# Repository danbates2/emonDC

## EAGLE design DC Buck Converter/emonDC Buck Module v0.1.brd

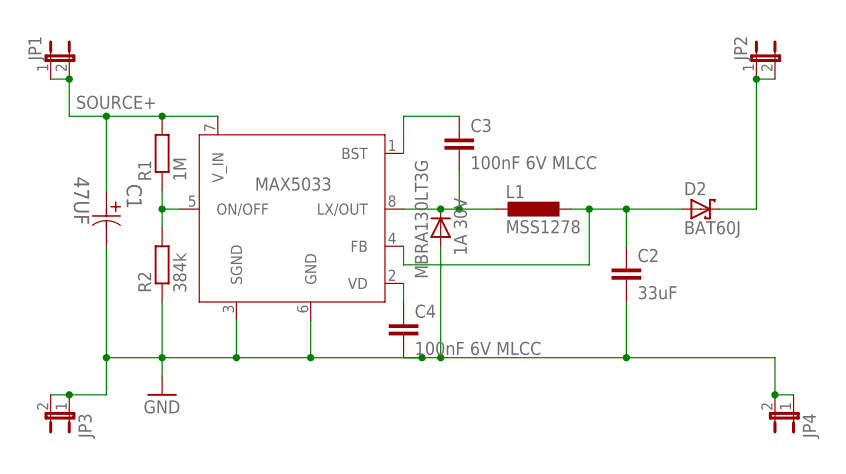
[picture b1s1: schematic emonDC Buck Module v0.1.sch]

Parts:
C1: 47UF; CAPAE1350X1400N
C2: 33uF; C1210; MPN TCQB336M006R0070
C3, C4: 100nF 6V MLCC; C0603
D1: MBRA130LT3G; DO-214; MPN MBRA130LT3G
D2: BAT60J; SOD323_ST
JP1, JP2, JP3, JP4: JP1E; JP1
L1: MSS1278; MPN MSS1278-224KLD
MAX5033: MAX5033BUSA+; 21-0111D_SBE-14
R1: 1M; R0603
R2: 384k; R0603

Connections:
+5V: D2.C, JP2.1, JP2.2
BST: C3.1, MAX5033.1 (BST)
FB: C2.1, D2.A, L1.P$1 (1), MAX5033.4 (FB)
GND: C1.2, C2.2, C4.2, D1.P$2 (A), JP3.1, JP3.2, JP4.1, JP4.2, MAX5033.3 (SGND), MAX5033.6 (GND), R2.1
ONOFF: MAX5033.5 (ON/OFF), R1.1, R2.2
OUT: C3.2, D1.P$1 (C), L1.P$2 (2), MAX5033.8 (LX/OUT)
SOURCE+: C1.1, JP1.1, JP1.2, MAX5033.7 (V_IN), R1.2
VD: C4.1, MAX5033.2 (VD)

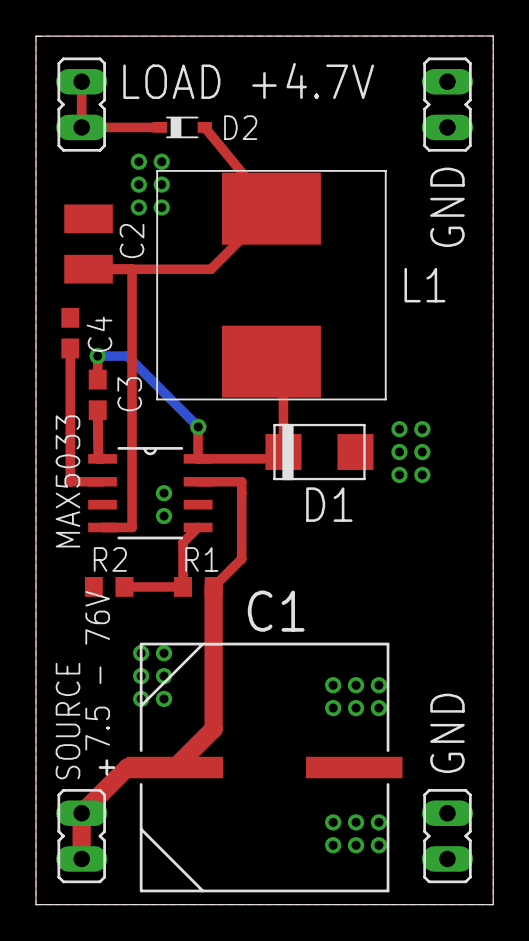
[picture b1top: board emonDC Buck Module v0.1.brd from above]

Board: 2 copper layers, 25.4 x 48.3 mm, 15 parts (1 on the bottom side), 8 nets.

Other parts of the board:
LOGO2: OSHW_LOGO_6MILX0200-NT; OSHW_6X200_NOTEXT

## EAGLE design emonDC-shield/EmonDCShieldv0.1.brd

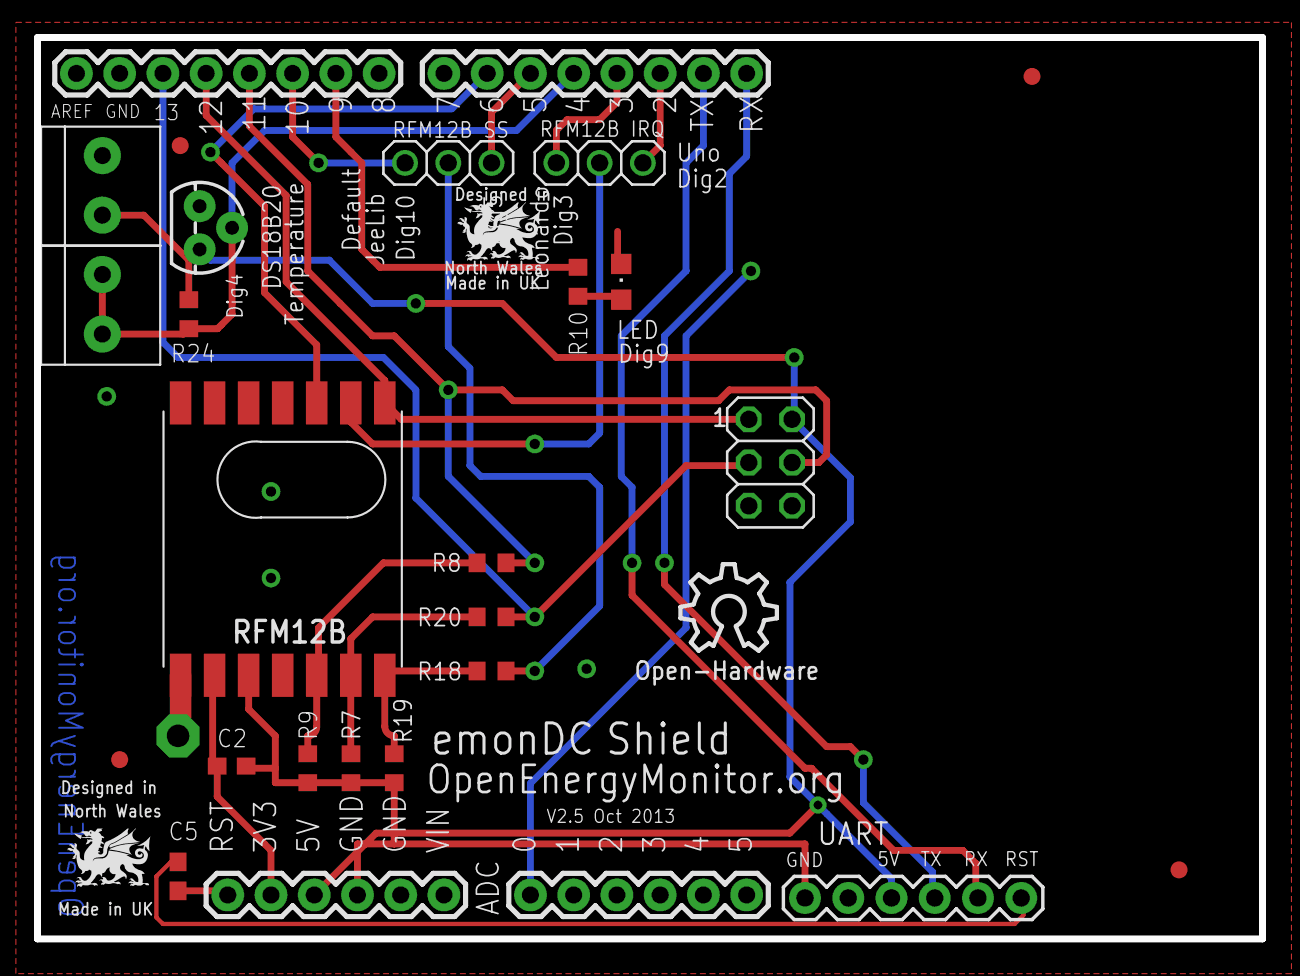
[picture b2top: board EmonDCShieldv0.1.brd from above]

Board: 2 copper layers, 72.0 x 53.0 mm, 26 parts (0 on the bottom side), 24 nets.

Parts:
ANT1: PAD-01
ARDUINO1: ARDUINO2
C2, C5: 100nF; C0603
ISP: 3x2F - BOTTOM; 2X03
J1, J2: 1X2-3.5MM
JP1, JP2: 1X03
JP3: FTDI_BASICPTH; FTDI_BASIC
LED: green; CHIPLED_0805
LOGO1: OSHW_LOGO_10MILX0200-NT; OSHW_10X200_NOTEXT
Q2: DS18B20; TO-92
R7, R9, R19: 10k; R0603
R8, R18, R20: 4k7; R0603
R10: 1K; R0603
R24: 4K7; R0603
U$1, U$3, U$4, U$5: FIDUCIAL; FIDUCIAL_1MM
U$2: RFM12B

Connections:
3.3V: ARDUINO1.3V3, C2.1, U$2.VDD
+5V: ARDUINO1.5V, ISP.2, J1.1, JP3.VCC, Q2.3, R24.1
DIG2: ARDUINO1.02, JP2.1
DIG3: ARDUINO1.PWM_03, JP2.3
DIG4: ARDUINO1.04, J2.1, J2.2, Q2.2, R24.2
DIG5: ARDUINO1.PWM_05, JP1.3
DIG6: ARDUINO1.PWM_06, U$2.FFS
DIG9: ARDUINO1.PWM_09, R10.2
DIG10: ARDUINO1.PWM_10, JP1.1
GND: ARDUINO1.GND, C2.2, ISP.6, J1.2, JP3.GND, LED.C, Q2.1, R7.1, R9.1, R19.1, U$2.GND
MISO: ARDUINO1.12, ISP.1, U$2.SDO
MOSI: ARDUINO1.PWM_11, ISP.4, R8.2
unnamed: JP2.2, U$2.IRQ
unnamed: JP1.2, R18.2
unnamed: C5.2, JP3.DTR
unnamed: LED.A, R10.1
unnamed: ANT1.1, U$2.ANT
unnamed: R7.2, R20.1, U$2.SCK
unnamed: R8.1, R9.2, U$2.SDI
unnamed: R18.1, R19.2, U$2.SEL
RST: ARDUINO1.RESET, C5.1
RX: ARDUINO1.RX_00, JP3.TXO
SCK: ARDUINO1.13, ISP.3, R20.2
TX: ARDUINO1.TX_01, JP3.RXI

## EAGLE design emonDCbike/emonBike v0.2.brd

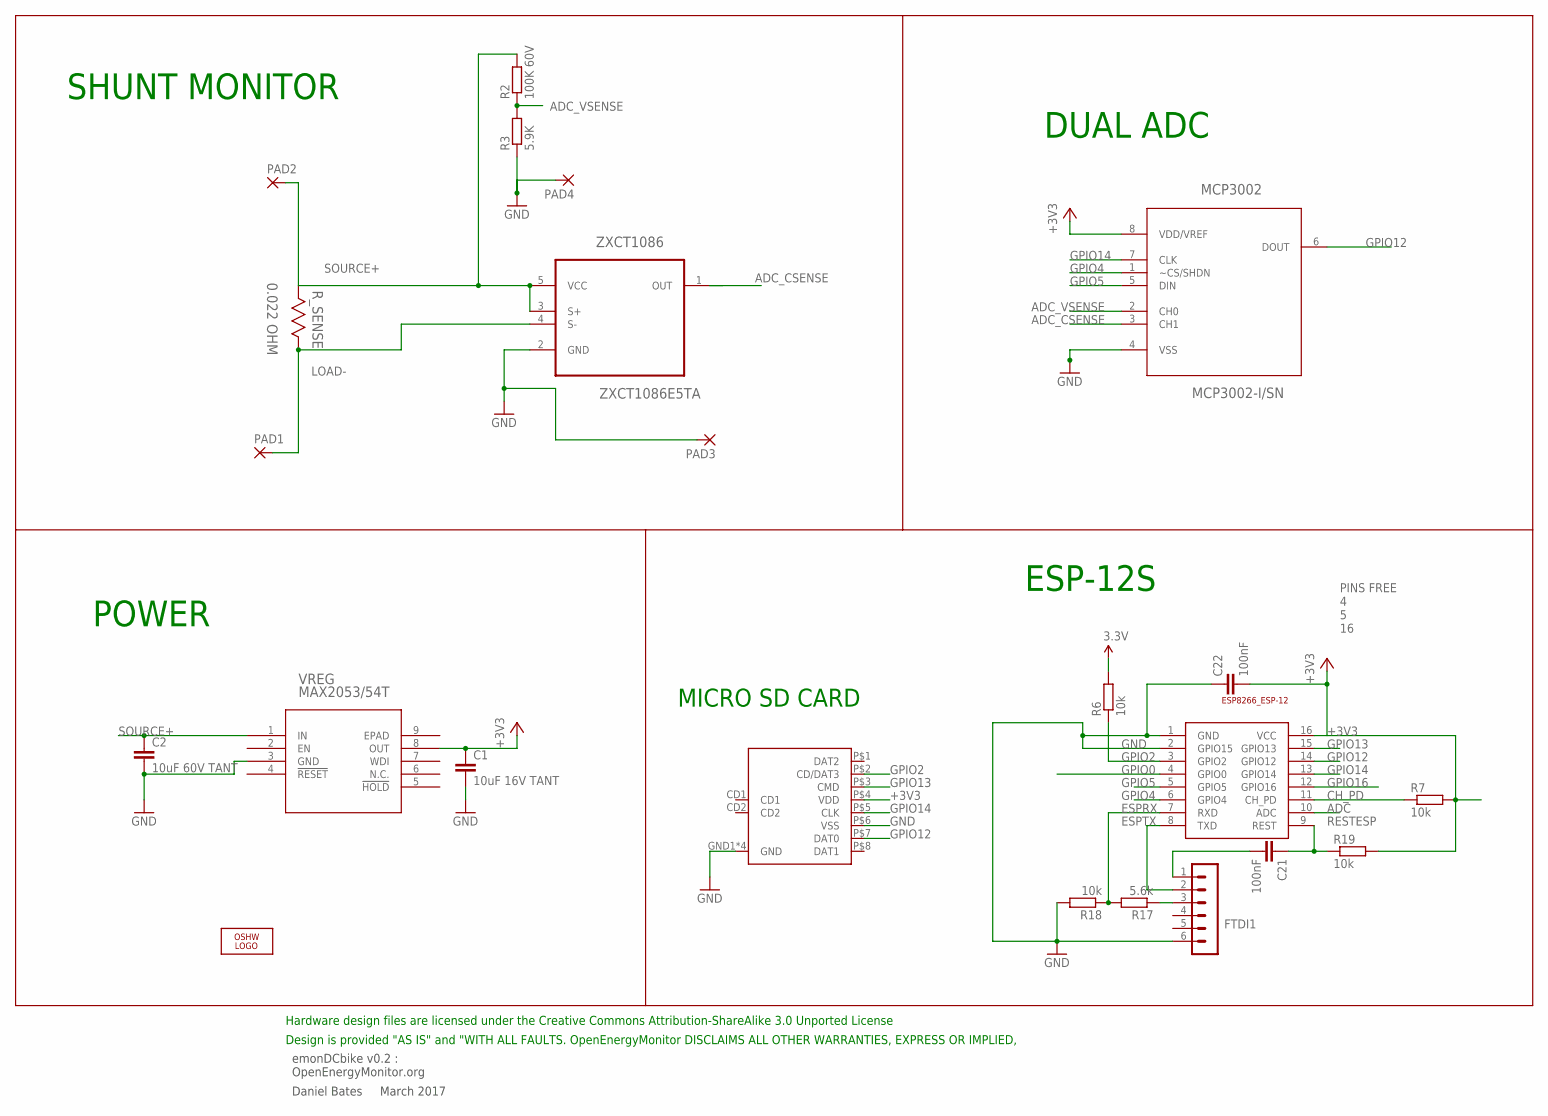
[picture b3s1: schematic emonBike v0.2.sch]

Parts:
C1: 10uF 16V TANT; C0603
C2: 10uF 60V TANT; C0603
C21, C22: 100nF; C0603
ESP-12: ESP8266_ESP-12; ESP8266-ESP12
FTDI1: FTDI-ESP; MA06-1
LOGO1: OSHW_LOGO_6MILX0200-NT; OSHW_6X200_NOTEXT
MAX2053: MAX5023TASA-T; 21-0111D_SBE-14
MCP3002: MCP3002-I/SN; SOIC127P600X175-8N
PAD1, PAD2, PAD3, PAD4: 3,81/1,4
R2: 100K 60V; R0603; MPN MCWR06X1003FTL
R3: 5.9K; R0603; MPN MCWR06X5901FTL
R6, R7, R18, R19: 10k; R0603
R17: 5.6k; R0603
R_SENSE: 0.022 OHM; RESC3216X71N
U$2: MOLEX_MICRO_SD_1040310811; MOLEX_MICROSD_EXPOSED
ZXCT1086: ZXCT1086E5TA; SOT95P280X130-5N

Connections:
+3V3: C1.1, C22.2, ESP-12.16 (VCC), MAX2053.8 (OUT), MCP3002.8 (VDD/VREF), R6.2, R7.2, R19.2, U$2.P$4 (VDD)
ADC: ESP-12.10 (ADC)
ADC_CSENSE: MCP3002.3 (CH1), ZXCT1086.1 (OUT)
ADC_VSENSE: MCP3002.2 (CH0), R2.1, R3.2
CH_PD: ESP-12.11 (CH_PD), R7.1
ESPRX: ESP-12.7 (RXD), R17.2, R18.1
ESPTX: ESP-12.8 (TXD), FTDI1.2
GND: C1.2, C2.2, C22.1, ESP-12.1 (GND), ESP-12.2 (GPIO15), FTDI1.6, MAX2053.3 (GND), MCP3002.4 (VSS), PAD3.1, PAD4.1, R3.1, R18.2, U$2.GND1 (GND), U$2.GND2 (GND), U$2.GND3 (GND), U$2.GND4 (GND), U$2.P$6 (VSS), ZXCT1086.2 (GND)
GPIO0: ESP-12.4 (GPIO0)
GPIO2: ESP-12.3 (GPIO2), R6.1, U$2.P$2 (CD/DAT3)
GPIO4: ESP-12.6 (GPIO4), MCP3002.1 (~CS/SHDN)
GPIO5: ESP-12.5 (GPIO5), MCP3002.5 (DIN)
GPIO12: ESP-12.14 (GPIO12), MCP3002.6 (DOUT), U$2.P$7 (DAT0)
GPIO13: ESP-12.15 (GPIO13), U$2.P$3 (CMD)
GPIO14: ESP-12.13 (GPIO14), MCP3002.7 (CLK), U$2.P$5 (CLK)
GPIO16: ESP-12.12 (GPIO16)
LOAD-: PAD1.1, R_SENSE.1 (R1), ZXCT1086.4 (S-)
unnamed: C21.2, FTDI1.1
unnamed: FTDI1.3, R17.1
RESTESP: C21.1, ESP-12.9 (REST), R19.1
SOURCE+: C2.1, MAX2053.1 (IN), PAD2.1, R2.2, R_SENSE.2 (R2), ZXCT1086.3 (S+), ZXCT1086.5 (VCC)

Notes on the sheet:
emonDCbike v0.2 : OpenEnergyMonitor.org
Daniel Bates March 2017
Design is provided "AS IS" and "WITH ALL FAULTS. OpenEnergyMonitor DISCLAIMS ALL OTHER WARRANTIES, EXPRESS OR IMPLIED,
Hardware design files are licensed under the Creative Commons Attribution-ShareAlike 3.0 Unported License
SHUNT MONITOR
ESP-12S
MICRO SD CARD
PINS FREE 4 5 16
POWER
DUAL ADC

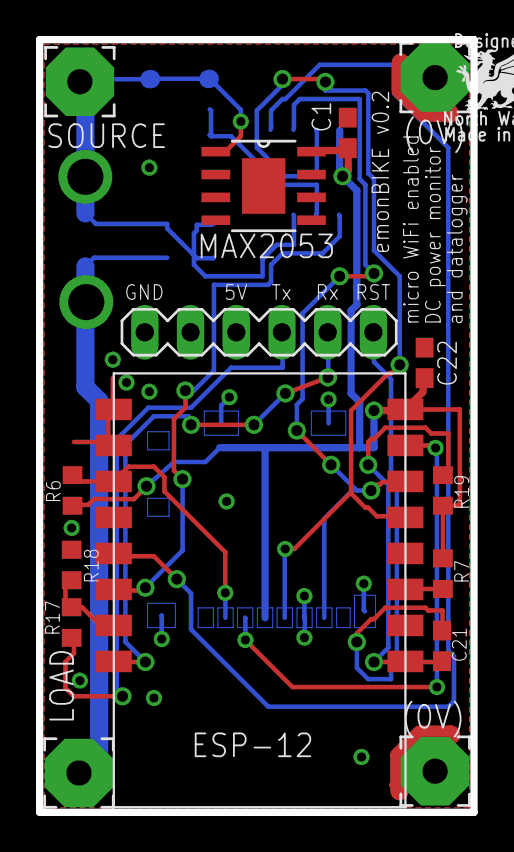
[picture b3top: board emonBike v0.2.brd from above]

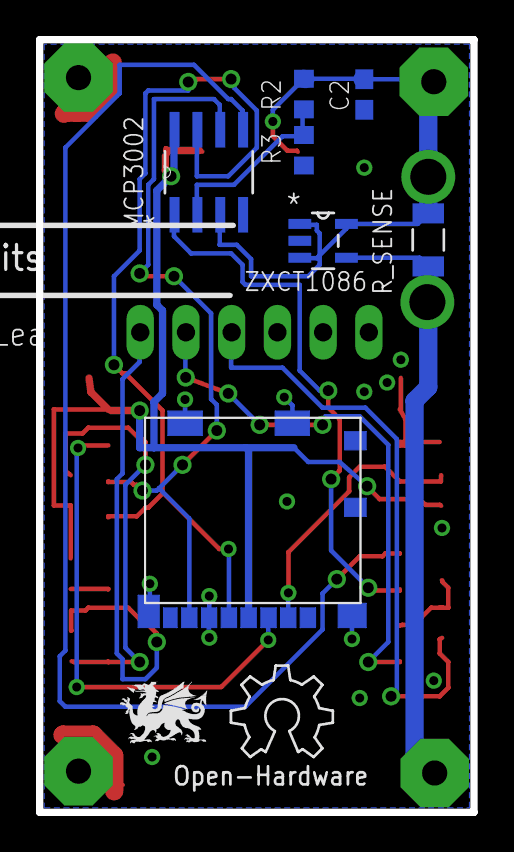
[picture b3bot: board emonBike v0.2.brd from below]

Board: 2 copper layers, 24.1 x 42.9 mm, 24 parts (9 on the bottom side), 18 nets.

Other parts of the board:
U$3: DRAGON_LOGO_NOTEXT

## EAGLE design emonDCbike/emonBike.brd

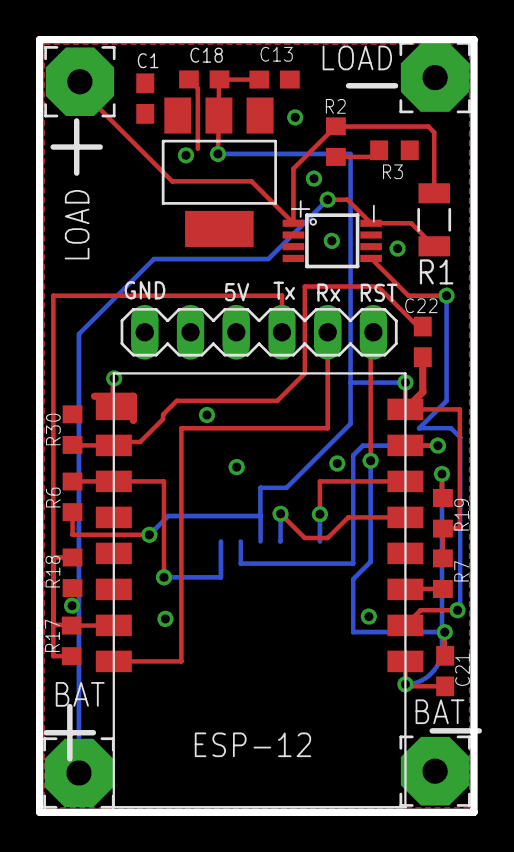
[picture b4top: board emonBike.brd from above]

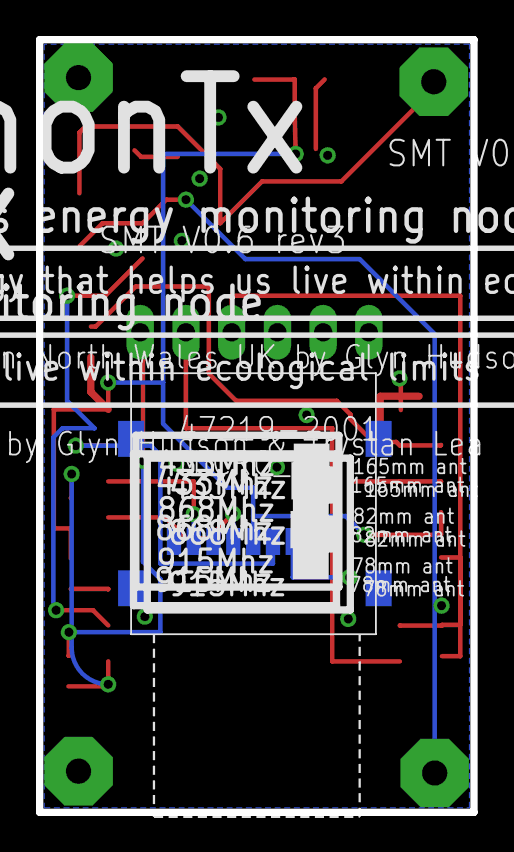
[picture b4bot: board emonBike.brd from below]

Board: 2 copper layers, 24.1 x 42.9 mm, 24 parts (2 on the bottom side), 18 nets.

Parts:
3.3V_REG: REG1117; SOT223
C1, C18: 10uF TANT; C0603
C13, C21, C22: 100nF; C0603
ESP-12: ESP8266_ESP-12; ESP8266-ESP12
FTDI1: FTDI-ESP; MA06-1
LOGO1: OSHW_LOGO_6MILX0200-NT; OSHW_6X200_NOTEXT
PAD1, PAD2, PAD3, PAD4: 3,81/1,4
R1: 0.022 OHM; RESC3216X71N
R2: 100K 60V; R0603
R3: 5.9K; R0603
R6, R7, R18, R19, R30: 10k; R0603
R17: 5.6k; R0603
SHUNTMON-A: LMP8481; S-PDSO-G08
U$1: 47219-2001_MICROSD

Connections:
3.3V: 3.3V_REG.2, C13.1, C18.1, C22.2, ESP-12.16, R6.2, R7.2, R19.2, U$1.PIN4
5.0V: 3.3V_REG.3, C1.1
ADC: ESP-12.10, SHUNTMON-A.5
ADCVSENSE-A: R2.1, R3.2
CH_PD: ESP-12.11, R7.1
ESPRX: ESP-12.7, R17.2, R18.1
ESPTX: ESP-12.8, FTDI1.2
GND: 3.3V_REG.1, C1.2, C13.2, C18.2, FTDI1.6, PAD3.1, PAD4.1, R3.1, R18.2, R30.1, SHUNTMON-A.4, SHUNTMON-A.6, SHUNTMON-A.7, U$1.P$1, U$1.P$2, U$1.P$3, U$1.P$4, U$1.PIN6
GPIO2: ESP-12.3, R6.1, U$1.PIN2
GPIO12: ESP-12.14, U$1.PIN7
GPIO13: ESP-12.15, U$1.PIN3
GPIO14: ESP-12.13, U$1.PIN5
GPIO15: C22.1, ESP-12.1, ESP-12.2, R30.2
INPUT-POS-A: PAD2.1, R1.2, R2.2, SHUNTMON-A.1
LOAD-NEG-A: PAD1.1, R1.1, SHUNTMON-A.8
unnamed: C21.2, FTDI1.1
unnamed: FTDI1.3, R17.1
RESTESP: C21.1, ESP-12.9, R19.1

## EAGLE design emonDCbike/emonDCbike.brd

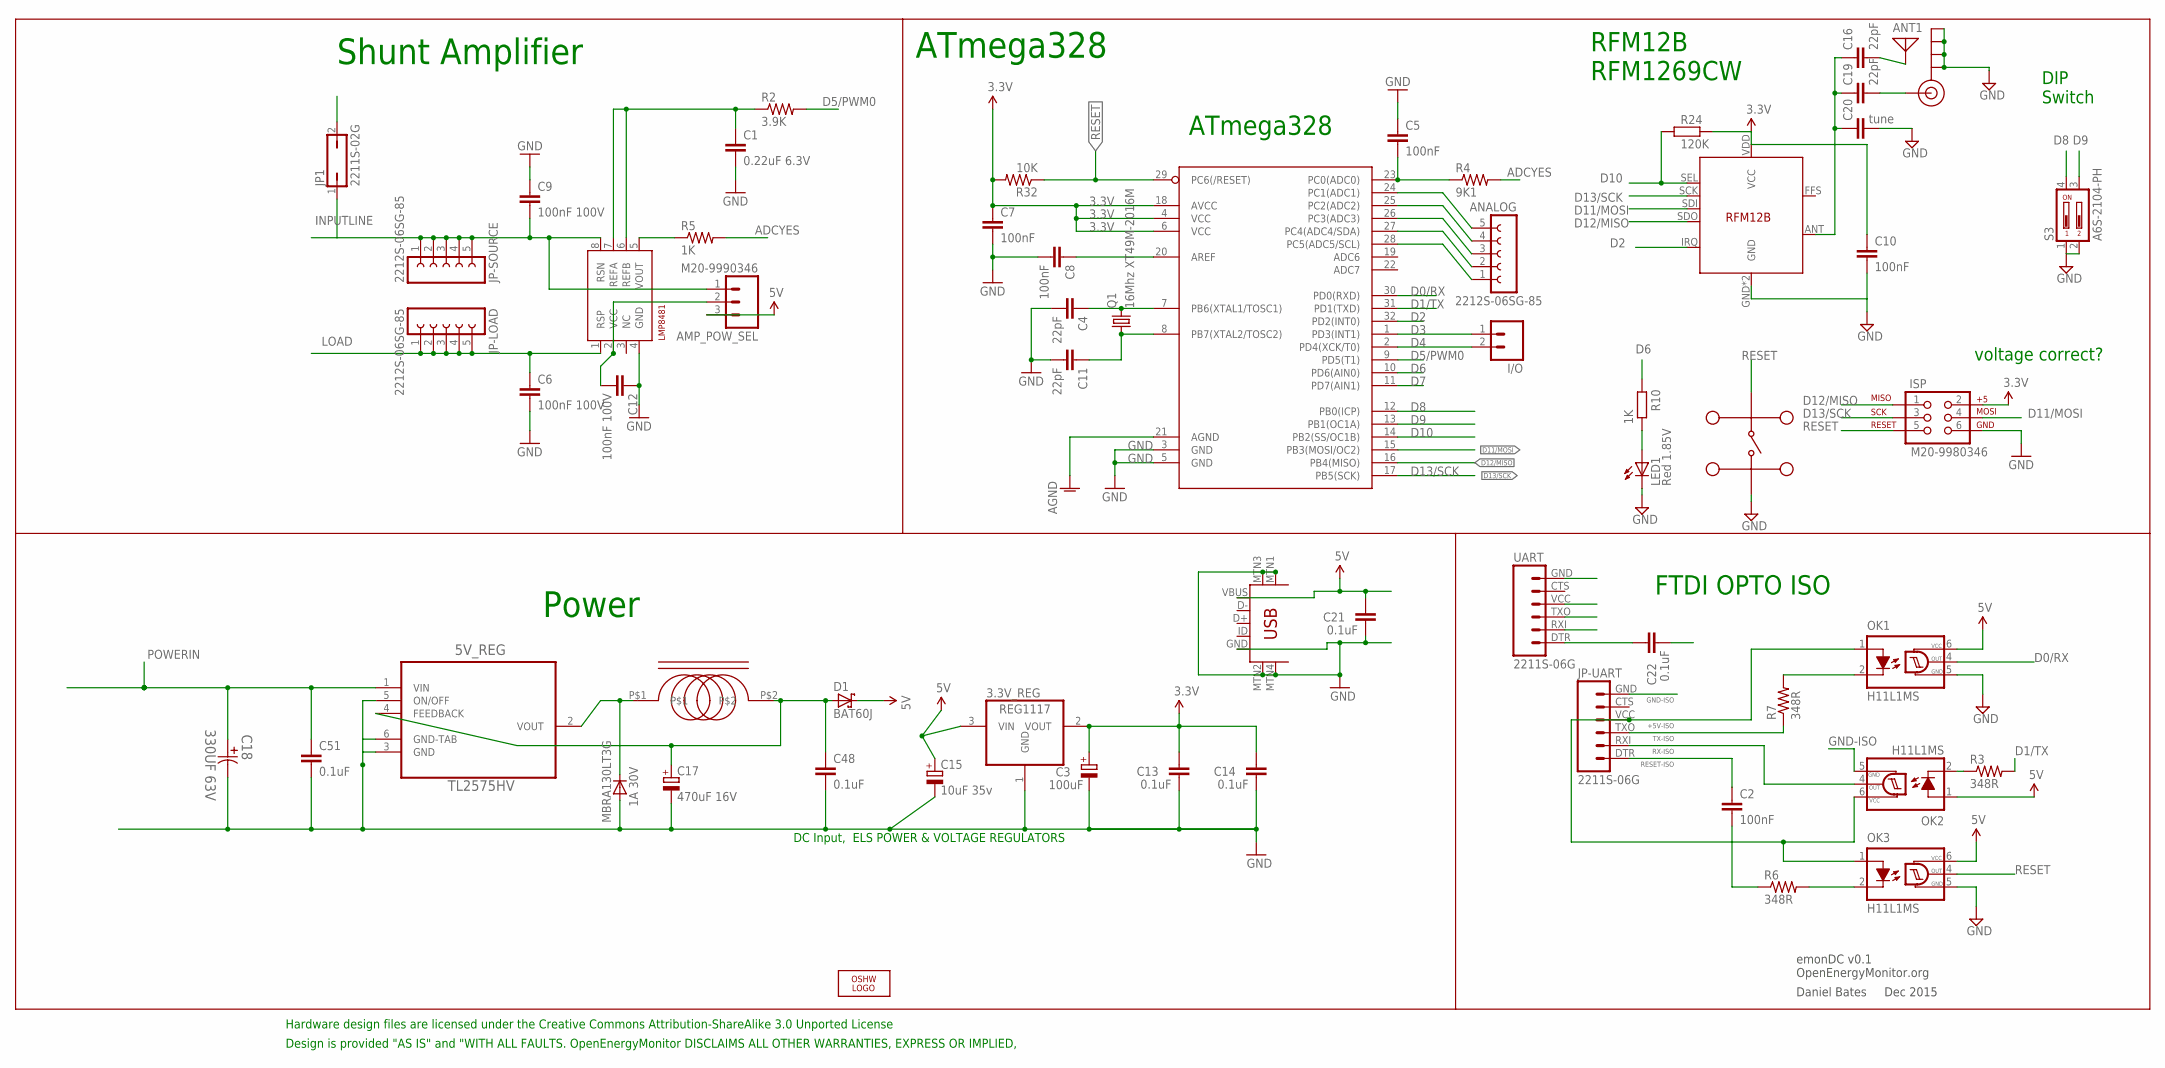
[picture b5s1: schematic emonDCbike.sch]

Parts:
3.3V_REG: REG1117; SOT223
5V_REG: TL2575HV; TO-263; MPN LM2575HVS-15/NOPB
AMP_POW_SEL: M20-9990346; 1X03_SMD_RA_FEMALE_NOWRITE; MPN M20-9990346
ANALOG: 2212S-06SG-85; FE05-1; MPN 2212S-06SG-85
ANT1: ANTENNA; PAD-01
C1: 0.22uF 6.3V; C0402K; MPN 04026D224KAT2A
C2, C5, C7, C8, C10: 100nF; C0402K; MPN 0402X104K100CT
C3: 100uF; 153CLV-0605; MPN UWX0J101MCL1GB
C4, C11, C16, C19: 22pF; C0603; MPN CC0402JRNPO9BN470
C6, C9, C12: 100nF 100V; C0805K; MPN 08051C104K4Z2A
C13, C14, C21, C22, C48: 0.1uF; C0805K; MPN 0805B104K160CT
C15: 10uF 35v; E1,8-4; MPN TAJD106K035RNJ
C17: 470uF 16V; E3,5-8; MPN 16YXF470MEFC10X12.5
C18: 330UF 63V; CAPPR500-1000X2000
C20: tune; C0603
C51: 0.1uF; C0805; MPN 0805B104K160CT
D1: BAT60J; SOD323_ST
D2: MBRA130LT3G; DO-214; MPN MBRA130LT3G
I1: SRR0603-331KL; MPN SRR0603-331KL
I/O: 2212S-02SG-85; 1X02_LOCK; MPN 2212S-02SG-85
ISP: M20-9980346; 2X3; MPN M20-9980346
J$1: SMA_EDGE; SMA-EDGE
JP1: 2211S-02G; JP1; MPN 2211S-02G
JP-LOAD: 2212S-06SG-85; FE05-1; MPN 2212S-06SG-85
JP-SOURCE: 2212S-06SG-85; FE05-1; MPN 2212S-06SG-85
JP-UART: 2211S-06G; FTDI_BASIC; MPN 2211S-06G
LED1: Red 1.85V; CHIP-LED0805; MPN SML-211UTT86K
LMP8481: LMP8481SMCLMP8481; S-PDSO-G08; MPN LMP8481MME-S/NOPB
LOGO1: OSHW_LOGO_6MILX0200-NT; OSHW_6X200_NOTEXT
OK1, OK2, OK3: H11L1MS; DIL6-SMD
Q1: 16Mhz XT49M-2016M; HC49UP; MPN XT49M-2016M
R2: 3.9K; R0603; MPN CRCW06039K09FKEA
R3, R6, R7: 348R; R0603; MPN MC0063W06031348R
R4: 9K1; R0603; MPN MC01W080559K1
R5, R10: 1K; R0603; MPN MC0063W060351K
R24: 120K; R0603; MPN RC0603FR-07120KL
R32: 10K; R0603; MPN MC0063W0603510K
RF: RFM12B
S3: A6S-2104-PH; DIP_SWITCH_SMT; MPN A6S2104H
U1_TQFP: ATMEGA328P; TQFP32-08; MPN ATMEGA328-AU
U$1: MC32882; SWITCH_TACT_MULTICOMP
UART: 2211S-06G; FTDI_BASIC; MPN 2211S-06G
USB: MUSB-05-S-B-SM-A; USB-MINIB-CISECO; MPN 67503-1020

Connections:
3.3V: 3.3V_REG.2 (VOUT), C3.+, C7.1, C10.1, C13.1, C14.1, ISP.2, R24.2, R32.2, RF.VDD (VCC), U1_TQFP.4 (VCC), U1_TQFP.6 (VCC), U1_TQFP.18 (AVCC)
5VHIGH: 5V_REG.4 (FEEDBACK), C17.+, C48.1, D1.A, I1.P$2
5VLOW: 3.3V_REG.3 (VIN), AMP_POW_SEL.3, C15.+, C21.1, D1.C, OK1.6 (VCC), OK2.1 (A), OK3.6 (VCC), UART.VCC (4), USB.VBUS
+5V-ISO: JP-UART.VCC (4), OK1.1 (A), OK2.6 (VCC), OK3.1 (A)
ADC1: ANALOG.5, U1_TQFP.24 (PC1(ADC1))
ADC2: ANALOG.4, U1_TQFP.25 (PC2(ADC2))
ADC3: ANALOG.3, U1_TQFP.26 (PC3(ADC3))
ADC4: ANALOG.2, U1_TQFP.27 (PC4(ADC4/SDA))
ADC5: ANALOG.1, U1_TQFP.28 (PC5(ADC5/SCL))
ADCYES: R4.2, R5.2
AGND: U1_TQFP.21 (AGND)
D0/RX: OK1.4 (OUT), U1_TQFP.30 (PD0(RXD)), UART.TXO (3)
D1/TX: R3.2, U1_TQFP.31 (PD1(TXD)), UART.RXI (2)
D2: RF.IRQ, U1_TQFP.32 (PD2(INT0))
D3: I/O.1, U1_TQFP.1 (PD3(INT1))
D4: I/O.2, U1_TQFP.2 (PD4(XCK/T0))
D5/PWM0: R2.2, U1_TQFP.9 (PD5(T1))
D6: R10.2, U1_TQFP.10 (PD6(AIN0))
D7: U1_TQFP.11 (PD7(AIN1))
D8: S3.4, U1_TQFP.12 (PB0(ICP))
D9: S3.3, U1_TQFP.13 (PB1(OC1A))
D9/PWM1: C1.1, LMP8481.6 (REFB), LMP8481.7 (REFA), R2.1
D10: R24.1, RF.SEL, U1_TQFP.14 (PB2(SS/OC1B))
D11/MOSI: ISP.4, RF.SDI, U1_TQFP.15 (PB3(MOSI/OC2))
D12/MISO: ISP.1, RF.SDO, U1_TQFP.16 (PB4(MISO))
D13/SCK: ISP.3, RF.SCK, U1_TQFP.17 (PB5(SCK))
DIG1: C16.1, C19.1, C20.1, RF.ANT
GND: 3.3V_REG.1 (GND), 5V_REG.3 (GND), 5V_REG.5 (ON/OFF), 5V_REG.6 (GND-TAB), C1.2, C3.-, C4.2, C5.1, C6.2, C7.2, C8.2, C9.1, C10.2, C11.2, C12.1, C13.2, C14.2, C15.-, C17.-, C18.2, C20.2, C21.2, C48.2, C51.2, D2.P$2 (A), ISP.6, J$1.GND@0 (GND), J$1.GND@1 (GND), J$1.GND@2 (GND), J$1.GND@3 (GND), LED1.C, LMP8481.4 (GND), OK1.5 (GND), OK3.5 (GND), RF.GND, RF.P$12 (GND), S3.1, S3.2, U1_TQFP.3 (GND), U1_TQFP.5 (GND), U$1.P$3, U$1.P$4, UART.GND (6), USB.GND, USB.MTN1 (MTN2), USB.MTN2 (MTN3), USB.MTN3 (MTN1), USB.MTN4
GND-ISO: JP-UART.GND (6), OK2.5 (GND)
IND: 5V_REG.2 (VOUT), D2.P$1 (C), I1.P$1
INPUTLINE: AMP_POW_SEL.1, C9.2, JP1.1, JP-SOURCE.1, JP-SOURCE.2, JP-SOURCE.3, JP-SOURCE.4, JP-SOURCE.5, LMP8481.8 (RSN)
LOAD: C6.1, JP-LOAD.1, JP-LOAD.2, JP-LOAD.3, JP-LOAD.4, JP-LOAD.5, LMP8481.1 (RSP)
unnamed: C4.1, Q1.2, U1_TQFP.7 (PB6(XTAL1/TOSC1))
unnamed: C5.2, R4.1, U1_TQFP.23 (PC0(ADC0))
unnamed: C22.1, UART.DTR (1)
unnamed: LMP8481.5 (VOUT), R5.1
unnamed: AMP_POW_SEL.2, C12.2, LMP8481.2 (VCC)
unnamed: C11.1, Q1.1, U1_TQFP.8 (PB7(XTAL2/TOSC2))
unnamed: C2.1, JP-UART.DTR (1)
unnamed: ANT1.1, C16.2
unnamed: OK1.2 (C), R7.2
unnamed: OK2.2 (C), R3.1
unnamed: OK3.2 (C), R6.2
unnamed: C8.1, U1_TQFP.20 (AREF)
unnamed: C19.2, J$1.SIG (SIGNAL)
unnamed: LED1.A, R10.1
POWERIN: 5V_REG.1 (VIN), C18.1, C51.1, JP1.2
RESET: C22.2, ISP.5, OK3.4 (OUT), R32.1, U1_TQFP.29 (PC6(/RESET)), U$1.P$1, U$1.P$2
RESET-ISO: C2.2, R6.1
RX-ISO: JP-UART.RXI (2), OK2.4 (OUT)
TX-ISO: JP-UART.TXO (3), R7.1

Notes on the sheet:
emonDC v0.1 OpenEnergyMonitor.org
Daniel Bates Dec 2015
Power
ATmega328
Design is provided "AS IS" and "WITH ALL FAULTS. OpenEnergyMonitor DISCLAIMS ALL OTHER WARRANTIES, EXPRESS OR IMPLIED,
Hardware design files are licensed under the Creative Commons Attribution-ShareAlike 3.0 Unported License
RFM12B RFM1269CW
DIP Switch
FTDI OPTO ISO
DC Input, ELS POWER & VOLTAGE REGULATORS
Shunt Amplifier
voltage correct?

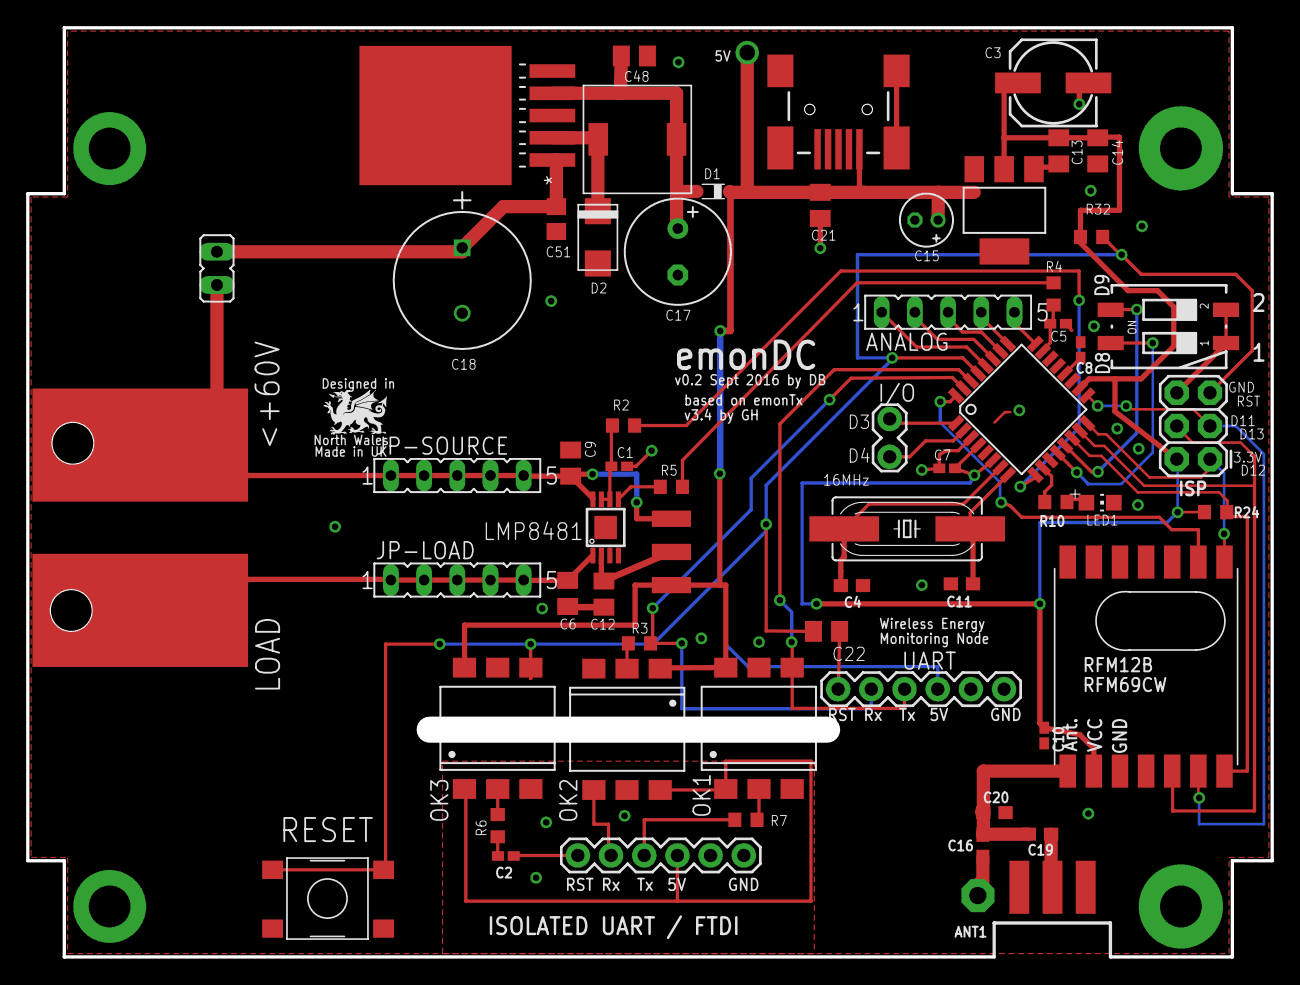
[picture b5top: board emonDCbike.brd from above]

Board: 2 copper layers, 95.2 x 71.1 mm, 61 parts (1 on the bottom side), 49 nets.

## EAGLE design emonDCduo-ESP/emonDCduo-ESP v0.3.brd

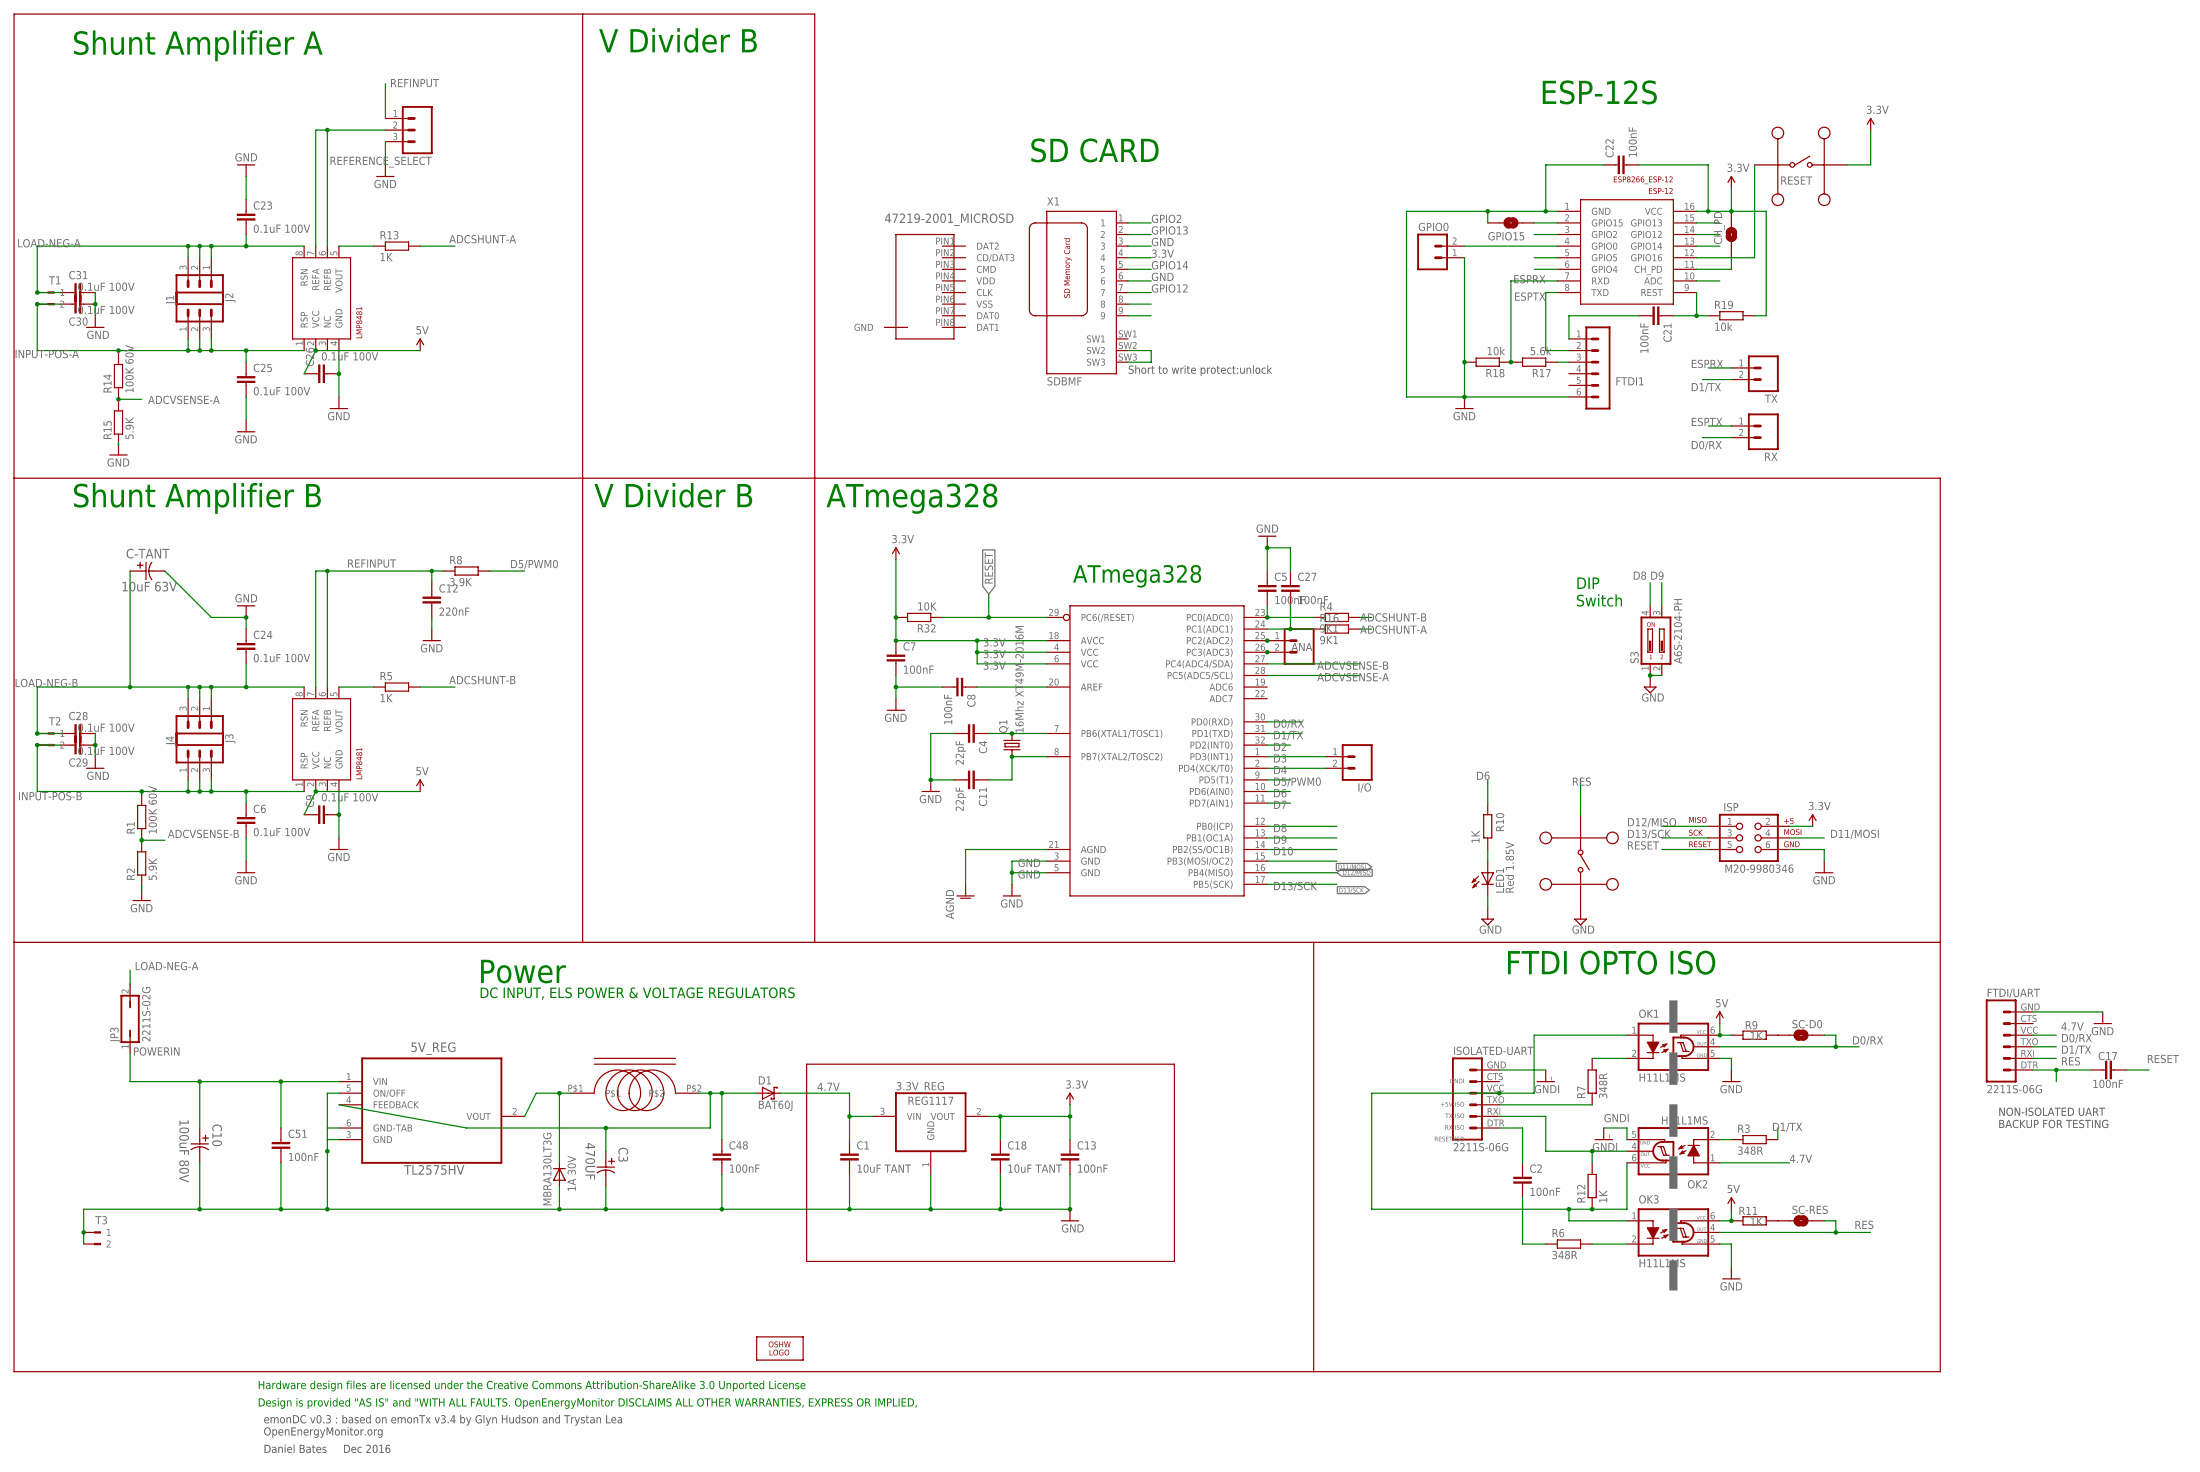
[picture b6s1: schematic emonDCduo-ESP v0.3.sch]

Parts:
3.3V_REG: REG1117; SOT223
5V_REG: TL2575HV; TO-263; MPN LM2575HVS-15/NOPB
ANA: 2212S-02SG-85; 1X02_LOCK; MPN 2212S-02SG-85
C1, C18: 10uF TANT; C0603
C2, C5, C7, C8, C13, C17, C21, C22, C27, C48, C51: 100nF; C0603
C3: 470UF; CAPAE830X1050N
C4, C11: 22pF; C0603
C6, C9, C23, C24, C25, C26, C28, C29, C30, C31: 0.1uF 100V; C0603; MPN C1608X7S2A104K080AB
C10: 100uF 80V; CAPAE1350X1400N
C12: 220nF; C0603
C-TANT: 10uF 63V; 2917; PARTNO 293D106X0063E2TE3
CH_PD: SOLDERJUMPERNO; SJ_2S-NO
D1: BAT60J; SOD323_ST
D2: MBRA130LT3G; DO-214; MPN MBRA130LT3G
ESP-12: ESP8266_ESP-12; ESP8266-ESP12
FTDI1: FTDI-ESP; MA06-1
FTDI/UART: 2211S-06G; FTDI_BASIC; MPN 2211S-06G
GPIO0: M02PTH; 1X02
GPIO15: SOLDERJUMPERNO; SJ_2S-NO
I1: SRR0603-331KL; MPN SRR0603-331KL
I/O: 2212S-02SG-85; 1X02_LOCK; MPN 2212S-02SG-85
ISOLATED-UART: 2211S-06G; FTDI_BASIC; MPN 2211S-06G
ISP: M20-9980346; 2X3; MPN M20-9980346
J1, J2, J3, J4: CONN_03; 1X03
JP3: 2211S-02G; JP1; MPN 2211S-02G
LED1: Red 1.85V; CHIP-LED0805; MPN SML-211UTT86K
LOGO1: OSHW_LOGO_6MILX0200-NT; OSHW_6X200_NOTEXT
MC1, MC32882: MC32882; SWITCH_TACT_MULTICOMP
OK1, OK2, OK3: H11L1MS; DIL6-SMD
Q1: 16Mhz XT49M-2016M; HC49UP; MPN XT49M-2016M
R1, R14: 100K 60V; R0603; MPN MCWR06X1003FTL
R2, R15: 5.9K; R0603; MPN MCWR06X5901FTL
R3, R6, R7: 348R; R0603
R4, R16: 9K1; R0603
R5, R9, R10, R11, R12, R13: 1K; R0603
R8: 3.9K; R0603
R17: 5.6k; R0603
R18, R19: 10k; R0603
R32: 10K; R0603
REFERENCE_SELECT: 2212S-02SG-85; 1X03; MPN 2212S-02SG-85
RX: M02PTH; 1X02
S3: A6S-2104-PH; DIP_SWITCH_SMT; MPN A6S2104H
SC-D0: SOLDERJUMPERNO; SJ_2S-NO
SC-RES: SOLDERJUMPERNO; SJ_2S-NO
SHUNTMON-A: LMP8481; S-PDSO-G08; MPN LMP8481MME-S/NOPB
SHUNTMON-B: LMP8481; S-PDSO-G08; MPN LMP8481MME-H/NOPB
T1, T2, T3: 180-2
TX: M02PTH; 1X02
U1_TQFP: ATMEGA328P; TQFP32-08; MPN ATMEGA328P-AU
U$1: 47219-2001_MICROSD
X1: SDBMF; SDBMF-009XXBXX2

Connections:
3.3V: 3.3V_REG.2 (VOUT), C7.1, C13.1, C18.1, C22.2, CH_PD.1, ESP-12.16 (VCC), ISP.2, MC1.P$3, MC1.P$4, R19.2, R32.2, U1_TQFP.4 (VCC), U1_TQFP.6 (VCC), U1_TQFP.18 (AVCC), X1.4
4.7V: 3.3V_REG.3 (VIN), C1.1, C9.1, C26.1, D1.C, FTDI/UART.VCC (4), OK1.6 (VCC), OK2.1 (A), OK3.6 (VCC), R9.2, R11.2, SHUNTMON-A.2 (VCC), SHUNTMON-B.2 (VCC)
5.0V: 5V_REG.4 (FEEDBACK), C3.1, C48.1, D1.A, I1.P$2
+5V-ISO: ISOLATED-UART.VCC (4), OK1.1 (A), OK2.6 (VCC), OK3.1 (A), R12.1
ADC2: ANA.1, U1_TQFP.25 (PC2(ADC2))
ADC3: ANA.2, U1_TQFP.26 (PC3(ADC3))
ADCSHUNT-A: R13.2, R16.2
ADCSHUNT-B: R4.2, R5.2
ADCVSENSE-A: R14.1, R15.2, U1_TQFP.28 (PC5(ADC5/SCL))
ADCVSENSE-B: R1.1, R2.2, U1_TQFP.27 (PC4(ADC4/SDA))
AGND: U1_TQFP.21 (AGND)
D0/RX: FTDI/UART.TXO (3), OK1.4 (OUT), RX.2, SC-D0.1, U1_TQFP.30 (PD0(RXD))
D1/TX: FTDI/UART.RXI (2), R3.2, TX.2, U1_TQFP.31 (PD1(TXD))
D2: U1_TQFP.32 (PD2(INT0))
D3: I/O.1, U1_TQFP.1 (PD3(INT1))
D4: I/O.2, U1_TQFP.2 (PD4(XCK/T0))
D5/PWM0: R8.2, U1_TQFP.9 (PD5(T1))
D6: R10.2, U1_TQFP.10 (PD6(AIN0))
D7: U1_TQFP.11 (PD7(AIN1))
D8: S3.4, U1_TQFP.12 (PB0(ICP))
D9: S3.3, U1_TQFP.13 (PB1(OC1A))
D10: U1_TQFP.14 (PB2(SS/OC1B))
D11/MOSI: ISP.4, U1_TQFP.15 (PB3(MOSI/OC2))
D12/MISO: ISP.1, U1_TQFP.16 (PB4(MISO))
D13/SCK: ISP.3, U1_TQFP.17 (PB5(SCK))
ESPRX: ESP-12.7 (RXD), R17.2, R18.1, TX.1
ESPTX: ESP-12.8 (TXD), FTDI1.2, RX.1
GND: 3.3V_REG.1 (GND), 5V_REG.3 (GND), 5V_REG.5 (ON/OFF), 5V_REG.6 (GND-TAB), C1.2, C3.2, C4.2, C5.1, C6.2, C7.2, C8.2, C9.2, C10.2, C11.2, C12.2, C13.2, C18.2, C22.1, C23.1, C24.1, C25.2, C26.2, C27.1, C28.2, C29.2, C30.2, C31.2, C48.2, C51.2, C-TANT.2, D2.P$2 (A), ESP-12.1 (GND), FTDI1.6, FTDI/UART.GND (6), GPIO0.1, GPIO15.2, ISP.6, LED1.C, MC32882.P$3, MC32882.P$4, OK1.5 (GND), OK3.5 (GND), R2.1, R15.1, R18.2, REFERENCE_SELECT.3, S3.1, S3.2, SHUNTMON-A.4 (GND), SHUNTMON-B.4 (GND), T3.1, T3.2, U1_TQFP.3 (GND), U1_TQFP.5 (GND), X1.3, X1.6
GNDI: ISOLATED-UART.GND (6), OK2.5 (GND)
GPIO2: ESP-12.3 (GPIO2), X1.1
GPIO4: ESP-12.6 (GPIO4)
GPIO5: ESP-12.5 (GPIO5)
GPIO12: ESP-12.14 (GPIO12), X1.7
GPIO13: ESP-12.15 (GPIO13), X1.2
GPIO14: ESP-12.13 (GPIO14), X1.5
GPIO16: ESP-12.12 (GPIO16), MC1.P$1, MC1.P$2
IND: 5V_REG.2 (VOUT), D2.P$1 (C), I1.P$1
INPUT-POS-A: C25.1, C30.1, J2.1, J2.2, J2.3, R14.2, SHUNTMON-A.1 (RSP), T1.2
INPUT-POS-B: C6.1, C29.1, J3.1, J3.2, J3.3, R1.2, SHUNTMON-B.1 (RSP), T2.2
LOAD-NEG-A: C23.2, C31.1, J1.1, J1.2, J1.3, JP3.2, SHUNTMON-A.8 (RSN), T1.1
LOAD-NEG-B: C24.2, C28.1, C-TANT.1, J4.1, J4.2, J4.3, SHUNTMON-B.8 (RSN), T2.1
unnamed: C4.1, Q1.2, U1_TQFP.7 (PB6(XTAL1/TOSC1))
unnamed: C5.2, R4.1, U1_TQFP.23 (PC0(ADC0))
unnamed: R11.1, SC-RES.2
unnamed: R13.1, SHUNTMON-A.5 (VOUT)
unnamed: R9.1, SC-D0.2
unnamed: R5.1, SHUNTMON-B.5 (VOUT)
unnamed: ESP-12.2 (GPIO15), GPIO15.1
unnamed: C11.1, Q1.1, U1_TQFP.8 (PB7(XTAL2/TOSC2))
unnamed: C2.1, ISOLATED-UART.DTR (1)
unnamed: X1.SW2, X1.SW3
unnamed: OK1.2 (C), R7.2
unnamed: OK2.2 (C), R3.1
unnamed: OK3.2 (C), R6.2
unnamed: C8.1, U1_TQFP.20 (AREF)
unnamed: C27.2, R16.1, U1_TQFP.24 (PC1(ADC1))
unnamed: REFERENCE_SELECT.2, SHUNTMON-A.6 (REFB), SHUNTMON-A.7 (REFA)
unnamed: ESP-12.4 (GPIO0), GPIO0.2
unnamed: C21.2, FTDI1.1
unnamed: FTDI1.3, R17.1
unnamed: CH_PD.2, ESP-12.11 (CH_PD)
unnamed: C21.1, ESP-12.9 (REST), R19.1
unnamed: LED1.A, R10.1
POWERIN: 5V_REG.1 (VIN), C10.1, C51.1, JP3.1
REFINPUT: C12.1, R8.1, REFERENCE_SELECT.1, SHUNTMON-B.6 (REFB), SHUNTMON-B.7 (REFA)
RES: C17.1, FTDI/UART.DTR (1), MC32882.P$1, MC32882.P$2, OK3.4 (OUT), SC-RES.1
RESET: C17.2, ISP.5, R32.1, U1_TQFP.29 (PC6(/RESET))
RESET-ISO: C2.2, R6.1
RX-ISO: ISOLATED-UART.RXI (2), OK2.4 (OUT), R12.2
TX-ISO: ISOLATED-UART.TXO (3), R7.1

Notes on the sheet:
emonDC v0.3 : based on emonTx v3.4 by Glyn Hudson and Trystan Lea OpenEnergyMonitor.org
Daniel Bates Dec 2016
Power
ATmega328
Design is provided "AS IS" and "WITH ALL FAULTS. OpenEnergyMonitor DISCLAIMS ALL OTHER WARRANTIES, EXPRESS OR IMPLIED,
Hardware design files are licensed under the Creative Commons Attribution-ShareAlike 3.0 Unported License
DIP Switch
FTDI OPTO ISO
DC INPUT, ELS POWER & VOLTAGE REGULATORS
Shunt Amplifier B
V Divider B
Shunt Amplifier A
RESET
ESP-12S
SD CARD
Short to write protect:unlock
NON-ISOLATED UART BACKUP FOR TESTING

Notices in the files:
parts and their libraries:
SparkFun-DigitalIC: Licensing: CC v3.0 Share-Alike You are welcome to use this library for commercial purposes.
SparkFun-Aesthetics: Licensing: Creative Commons ShareAlike 4.0 International - https://creativecommons.org/licenses/by-sa/4.0
